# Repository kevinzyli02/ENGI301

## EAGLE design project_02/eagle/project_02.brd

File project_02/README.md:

Attached is the PCB design for my PocketBeagle project. Attached are the relevant libraries, schematics, board files, GRB files, and description under docs

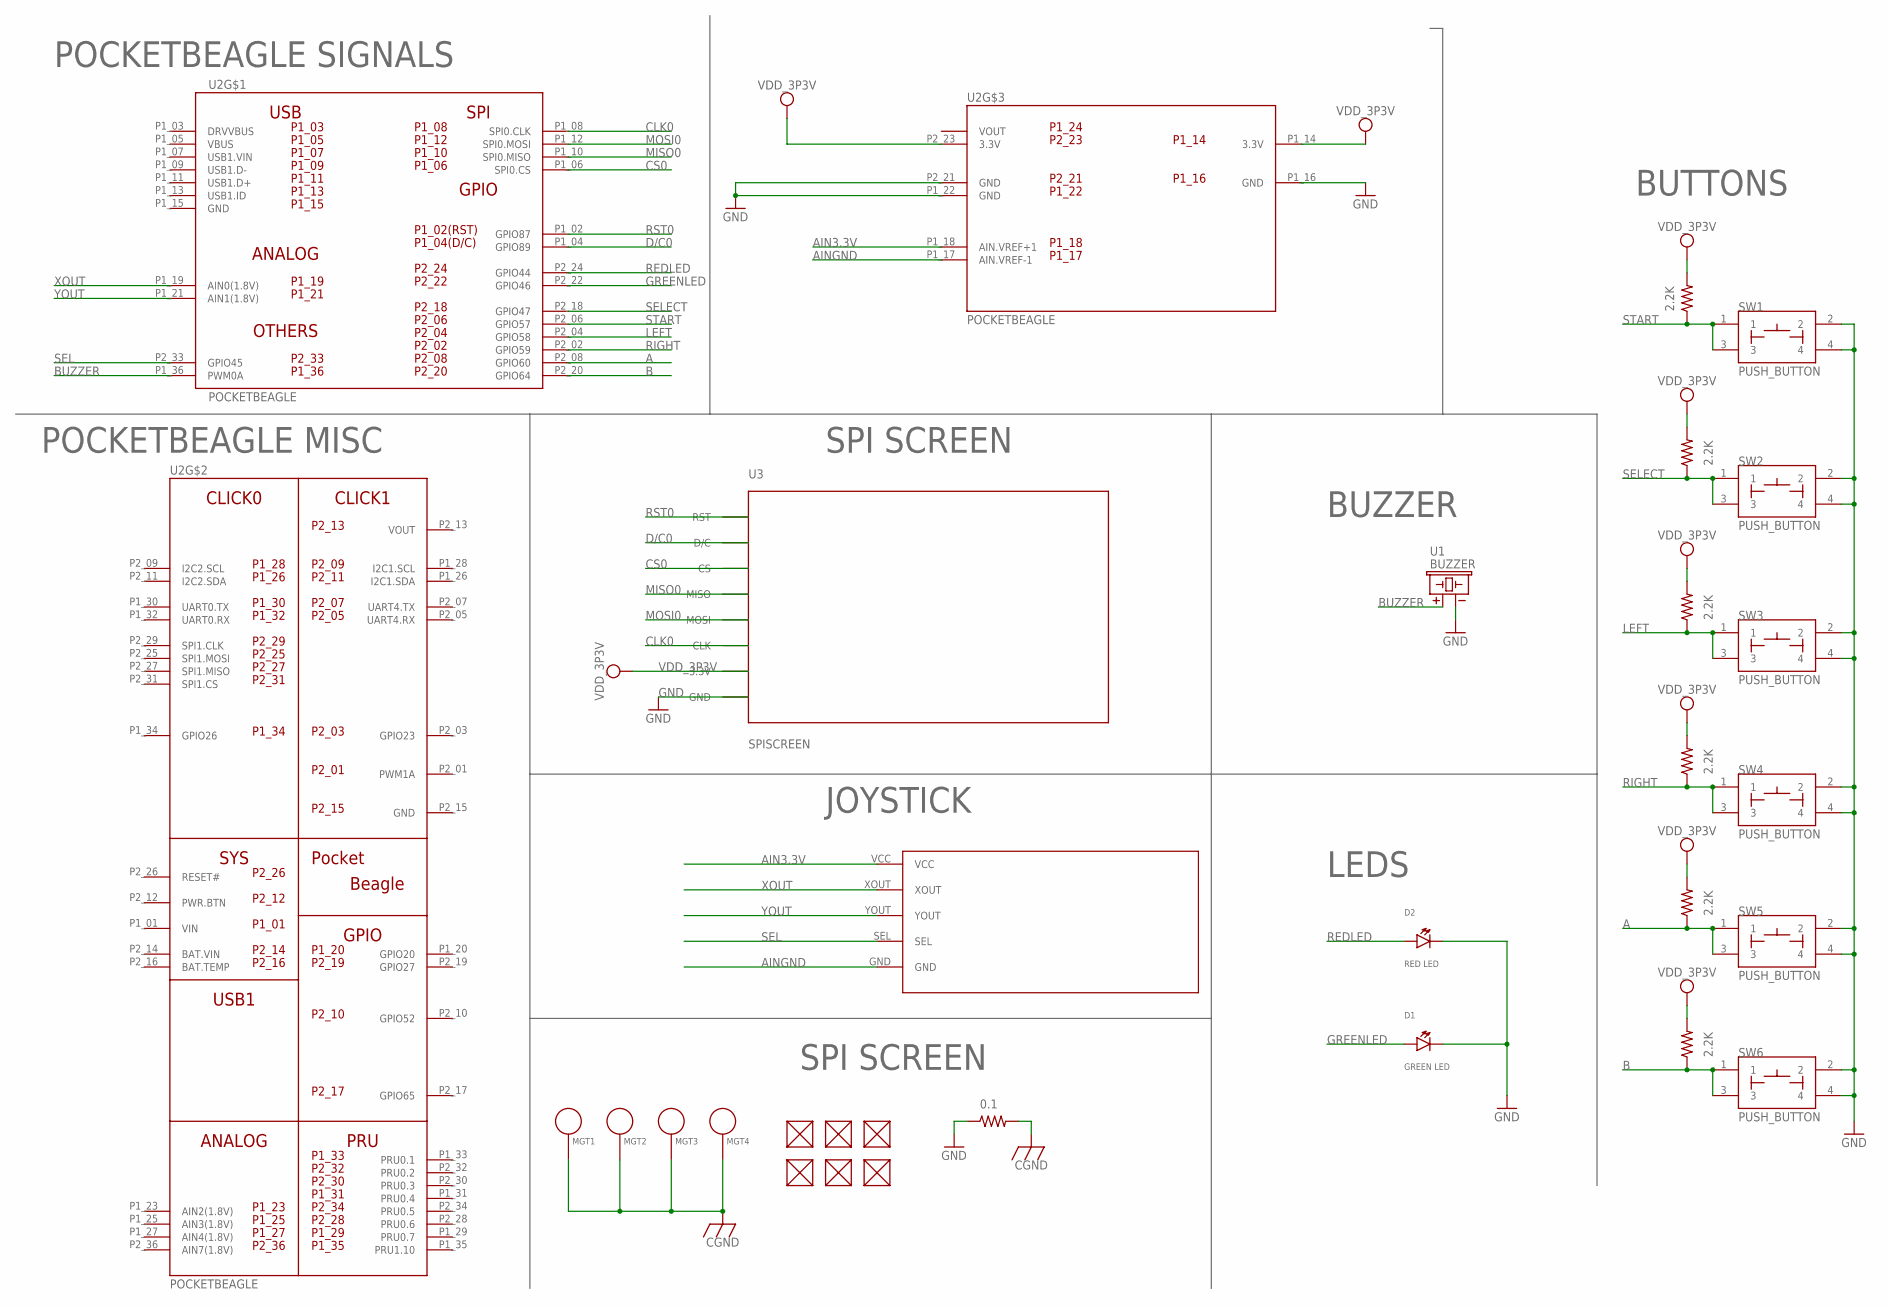
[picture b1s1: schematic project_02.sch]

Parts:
2.2K: 2.2K; R0402
D1: GREEN LED; EIA-STD
D2: RED LED; EIA-STD
FUD1, FUD2, FUD3, FUD4, FUD5, FUD6: FIDUCIAL; FIDUCIAL_40MIL
MGT1, MGT2, MGT3, MGT4: MOUNTING_HOLE
R1: 0.1; R0402
R3, R4, R5, R6, R7: 2.2K; R0402
SW1, SW2, SW3, SW4, SW5, SW6: PUSH_BUTTON; BUTTON_12.5MM
U1: BUZZER; BUZZER_6.5MM
U2: POCKETBEAGLE
U3: SPISCREEN; SCREEN
U$1: JOYSTICK2

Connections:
A: R6.1, SW5.1, SW5.3, U2.P2_08 (GPIO60)
AIN3.3V: U2.P1_18 (AIN.VREF+1), U$1.VCC
AINGND: U2.P1_17 (AIN.VREF-1), U$1.GND
B: R7.1, SW6.1, SW6.3, U2.P2_20 (GPIO64)
BAT.VIN: U2.P2_14 (BAT.VIN)
BUZZER: U1.+, U2.P1_36 (PWM0A)
CGND: MGT1.P$1, MGT2.P$1, MGT3.P$1, MGT4.P$1, R1.2
CLK0: U2.P1_08 (SPI0.CLK), U3.CLK
CS0: U2.P1_06 (SPI0.CS), U3.CS
D/C0: U2.P1_04 (GPIO89), U3.D/C
GND: D1.CATHODE, D2.CATHODE, R1.1, SW1.2, SW1.4, SW2.2, SW2.4, SW3.2, SW3.4, SW4.2, SW4.4, SW5.2, SW5.4, SW6.2, SW6.4, U1.-, U2.P1_16 (GND), U2.P1_22 (GND), U2.P2_15 (GND), U2.P2_21 (GND), U3.GND
GREENLED: D1.ANODE, U2.P2_22 (GPIO46)
LEFT: R4.1, SW3.1, SW3.3, U2.P2_04 (GPIO58)
MISO0: U2.P1_10 (SPI0.MISO), U3.MISO
MOSI0: U2.P1_12 (SPI0.MOSI), U3.MOSI
REDLED: D2.ANODE, U2.P2_24 (GPIO44)
RIGHT: R5.1, SW4.1, SW4.3, U2.P2_02 (GPIO59)
RST0: U2.P1_02 (GPIO87), U3.RST
SEL: U2.P2_33 (GPIO45), U$1.SEL
SELECT: R3.1, SW2.1, SW2.3, U2.P2_18 (GPIO47)
START: 2.2K.1, SW1.1, SW1.3, U2.P2_06 (GPIO57)
VDD_3P3V: 2.2K.2, R3.2, R4.2, R5.2, R6.2, R7.2, U2.P1_14 (3.3V), U2.P2_23 (3.3V), U3.3.3V
VIN: U2.P1_01 (VIN)
VOUT: U2.P1_24 (VOUT), U2.P2_13 (VOUT)
XOUT: U2.P1_19 (AIN0(1.8V)), U$1.XOUT
YOUT: U2.P1_21 (AIN1(1.8V)), U$1.YOUT

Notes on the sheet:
BUTTONS
LEDS
BUZZER
JOYSTICK
SPI SCREEN
POCKETBEAGLE SIGNALS
POCKETBEAGLE MISC

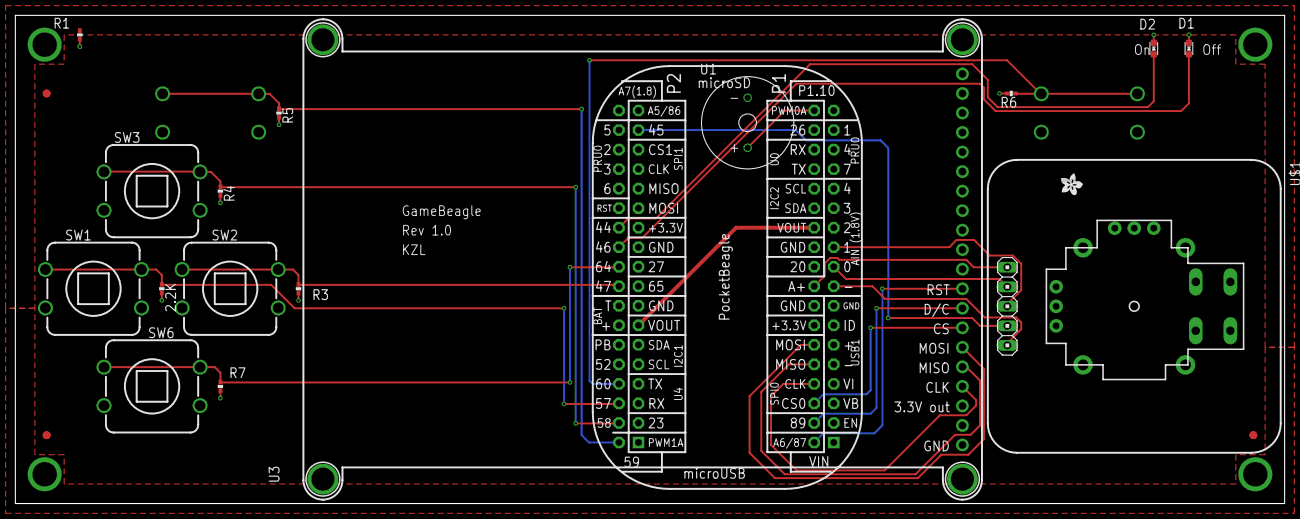
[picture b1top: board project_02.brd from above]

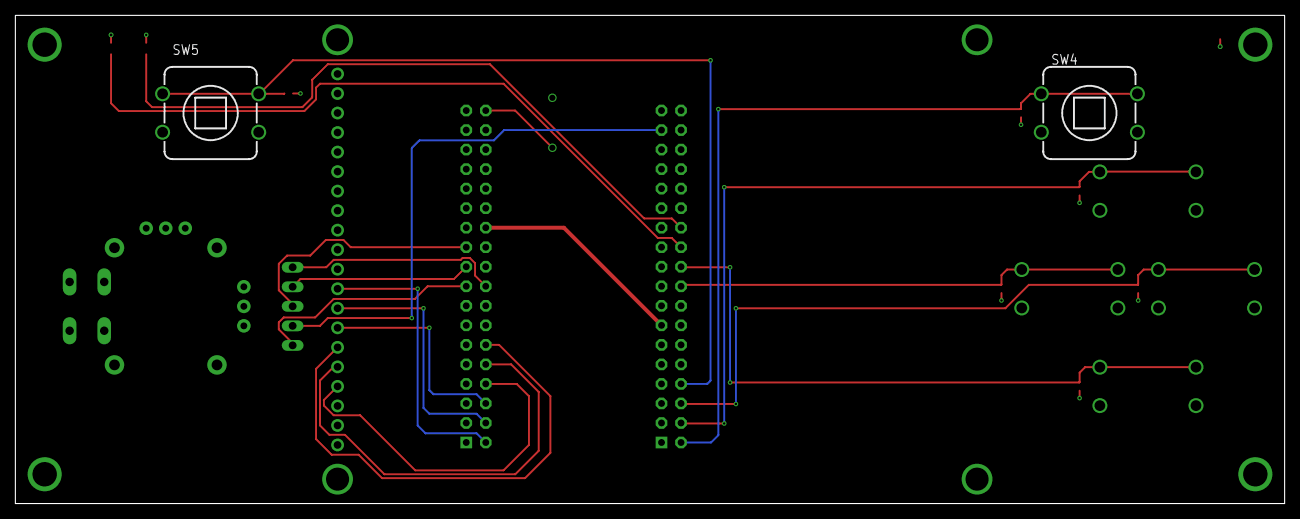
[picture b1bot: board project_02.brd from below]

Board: 4 copper layers, 165.1 x 63.5 mm, 29 parts (2 on the bottom side), 24 nets.

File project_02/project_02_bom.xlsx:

Designator | Value | Footprint | Populate | MPN | Manufacturer | MPN | Manufacturer | Description
2.2K | 2.2K | R0402 | 1 | MF-RES-0402-1K | MacroFab |  |  | Resistors for buttons
D1 | GREEN LED | EIA-STD | 1 | MF-LED-0805-GREEN | MacroFab |  |  | Green LED
D2 | RED LED | EIA-STD | 1 | MF-LED-0603-RED | MacroFab |  |  | Red LED
FUD1 | FIDUCIAL | FIDUCIAL_40MIL | 0 | 5-1567064-5 | TE Connectivity / AMP |  |  | Fiducials
FUD2 | FIDUCIAL | FIDUCIAL_40MIL | 0 | 5-1567064-5 | TE Connectivity / AMP |  |  | Fiducials
FUD3 | FIDUCIAL | FIDUCIAL_40MIL | 0 | 5-1567064-5 | TE Connectivity / AMP |  |  | Fiducials
FUD4 | FIDUCIAL | FIDUCIAL_40MIL | 0 | 5-1567064-5 | TE Connectivity / AMP |  |  | Fiducials
FUD5 | FIDUCIAL | FIDUCIAL_40MIL | 0 | 5-1567064-5 | TE Connectivity / AMP |  |  | Fiducials
FUD6 | FIDUCIAL | FIDUCIAL_40MIL | 0 | 5-1567064-5 | TE Connectivity / AMP |  |  | Fiducials
MGT1 | MOUNTING_HOLE | MOUNTING_HOLE | 0 | HIF3-SPACER FOR MOUNTING HOLE | HIROSE ELECTRIC |  |  | Mounting Holes
MGT2 | MOUNTING_HOLE | MOUNTING_HOLE | 0 | HIF3-SPACER FOR MOUNTING HOLE | HIROSE ELECTRIC |  |  | Mounting Holes
MGT3 | MOUNTING_HOLE | MOUNTING_HOLE | 0 | HIF3-SPACER FOR MOUNTING HOLE | HIROSE ELECTRIC |  |  | Mounting Holes
MGT4 | MOUNTING_HOLE | MOUNTING_HOLE | 0 | HIF3-SPACER FOR MOUNTING HOLE | HIROSE ELECTRIC
R1 | 0.1 | R0402 | 0 | WSL0805R1000FEA | Vishay |  |  | 01 Ohm Resistor
R3 | 2.2K | R0402 | 1 | MF-RES-0402-1K | MacroFab |  |  | 1K resistor which replaces 2.2K resistor
R4 | 2.2K | R0402 | 1 | MF-RES-0402-1K | MacroFab |  |  | 1K resistor which replaces 2.2K resistor
R5 | 2.2K | R0402 | 1 | MF-RES-0402-1K | MacroFab |  |  | 1K resistor which replaces 2.2K resistor
R6 | 2.2K | R0402 | 1 | MF-RES-0402-1K | MacroFab |  |  | 1K resistor which replaces 2.2K resistor
R7 | 2.2K | R0402 | 1 | MF-RES-0402-1K | MacroFab |  |  | 1K resistor which replaces 2.2K resistor
SW1 | PUSH_BUTTON | BUTTON_12.5MM | 0 | MKSACPUSHBUTTONORANGE | Omron |  |  | Push button
SW2 | PUSH_BUTTON | BUTTON_12.5MM | 0 | MKSACPUSHBUTTONORANGE | Omron |  |  | Push button
SW3 | PUSH_BUTTON | BUTTON_12.5MM | 0 | MKSACPUSHBUTTONORANGE | Omron |  |  | Push button
SW4 | PUSH_BUTTON | BUTTON_12.5MM | 0 | MKSACPUSHBUTTONORANGE | Omron |  |  | Push button
SW5 | PUSH_BUTTON | BUTTON_12.5MM | 0 | MKSACPUSHBUTTONORANGE | Omron |  |  | Push button
SW6 | PUSH_BUTTON | BUTTON_12.5MM | 0 | MKSACPUSHBUTTONORANGE | Omron |  |  | Push button
U$1 | JOYSTICK2 | JOYSTICK2 | 0 | SPARKY JOYSTICK 22NF | SigmasTek |  |  | Joystick
U1 | BUZZER | BUZZER_6.5MM | 1 | 64580075 | Werma | PKB24SPCH3601-B0 | Murata | Buzzer
U2 | POCKETBEAGLE | POCKETBEAGLE | 0 | POCKETBEAGLE | BeagleBoard |  |  | Pocketbeagle
U3 | SPISCREEN | SCREEN | 0 | 1743 | Adafruit Industries |  |  | SPI Screen

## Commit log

2023-10-02 Adding comments
2023-10-30 Issues with previous code
2023-11-02 backup after reflashing
2023-11-06 revisions 11-6-23
2023-11-13 update 11/13
2023-11-15 Update run
2023-11-27 new roms
2023-12-13 Create newhahaha
2023-12-13 Create hahaha
